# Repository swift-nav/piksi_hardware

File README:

Piksi Hardware
==============

Electronics design files for Swift Navigation projects - Eagle libraries,
schematics, and board files.

Copyright
=========

All files copyright (C) 2011-2013 Swift Navigation Inc.

License
=======

All files in this repository are licensed under the Creative Commons
Attribution Share-Alike 3.0 license - text available in LICENSE.

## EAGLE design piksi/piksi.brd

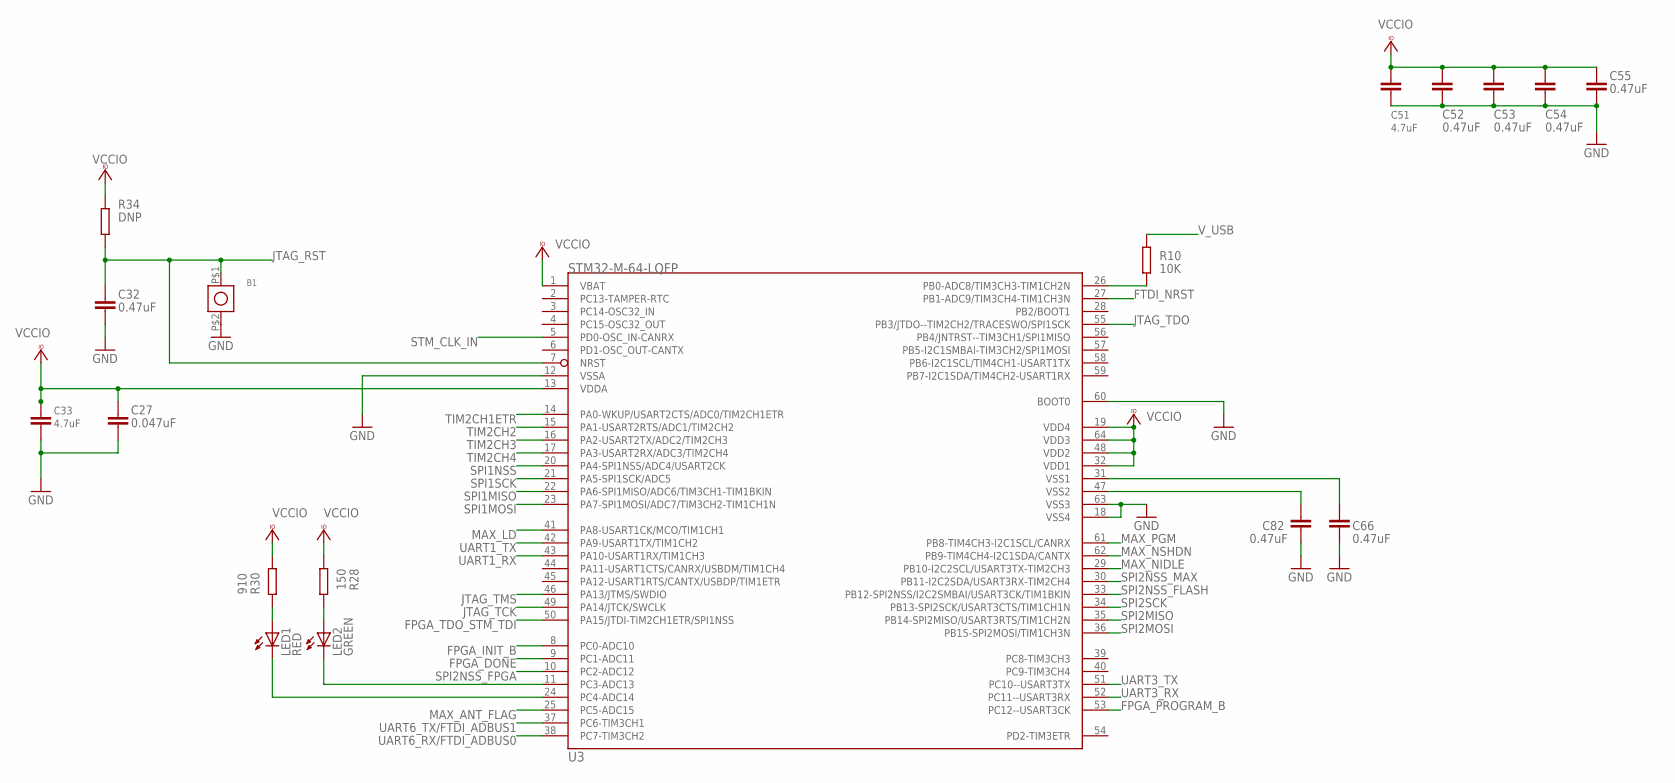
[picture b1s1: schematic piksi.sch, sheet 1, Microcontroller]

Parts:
B1: B3U-1000P
C27: 0.047uF; 0402-CAP
C32, C52, C53, C54, C55, C66, C82: 0.47uF; 0402-CAP
C33, C51: 4.7uF; 0603-CAP
LED1: RED; 0603-LED
LED2: GREEN; 0603-LED
R10: 10K; 0402-RES
R28: 150; 0402-RES
R30: 910; 0402-RES
R34: DNP; 0402-RES
U3: STM32-M-64-LQFP; LQFP64

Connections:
FPGA_DONE: U3.9 (PC1-ADC11); also elsewhere on the board
FPGA_INIT_B: U3.8 (PC0-ADC10); also elsewhere on the board
FPGA_PROGRAM_B: U3.53 (PC12--USART3CK); also elsewhere on the board
FPGA_TDO_STM_TDI: U3.50 (PA15/JTDI-TIM2CH1ETR/SPI1NSS); also elsewhere on the board
FTDI_NRST: U3.27 (PB1-ADC9/TIM3CH4-TIM1CH3N); also elsewhere on the board
GND: B1.P$2 (2), C27.P$2 (2), C32.P$2 (2), C33.P$1 (1), C51.P$1 (1), C52.P$2 (2), C53.P$2 (2), C54.P$2 (2), C55.P$2 (2), C66.P$2 (2), C82.P$1 (1), U3.12 (VSSA), U3.18 (VSS4), U3.60 (BOOT0), U3.63 (VSS3); also elsewhere on the board
JTAG_RST: B1.P$1 (1), C32.P$1 (1), R34.P$1 (1), U3.7 (NRST); also elsewhere on the board
JTAG_TCK: U3.49 (PA14/JTCK/SWCLK); also elsewhere on the board
JTAG_TDO: U3.55 (PB3/JTDO--TIM2CH2/TRACESWO/SPI1SCK); also elsewhere on the board
JTAG_TMS: U3.46 (PA13/JTMS/SWDIO); also elsewhere on the board
MAX_ANT_FLAG: U3.25 (PC5-ADC15); also elsewhere on the board
MAX_LD: U3.41 (PA8-USART1CK/MCO/TIM1CH1); also elsewhere on the board
MAX_NIDLE: U3.29 (PB10-I2C2SCL/USART3TX-TIM2CH3); also elsewhere on the board
MAX_NSHDN: U3.62 (PB9-TIM4CH4-I2C1SDA/CANTX); also elsewhere on the board
MAX_PGM: U3.61 (PB8-TIM4CH3-I2C1SCL/CANRX); also elsewhere on the board
unnamed: R10.P$1 (1), U3.26 (PB0-ADC8/TIM3CH3-TIM1CH2N)
unnamed: LED1.A, R30.P$1 (1)
unnamed: LED1.C, U3.24 (PC4-ADC14)
unnamed: LED2.A, R28.P$2 (2)
unnamed: LED2.C, U3.11 (PC3-ADC13)
SPI1MISO: U3.22 (PA6-SPI1MISO/ADC6/TIM3CH1-TIM1BKIN); also elsewhere on the board
SPI1MOSI: U3.23 (PA7-SPI1MOSI/ADC7/TIM3CH2-TIM1CH1N); also elsewhere on the board
SPI1NSS: U3.20 (PA4-SPI1NSS/ADC4/USART2CK); also elsewhere on the board
SPI1SCK: U3.21 (PA5-SPI1SCK/ADC5); also elsewhere on the board
SPI2MISO: U3.35 (PB14-SPI2MISO/USART3RTS/TIM1CH2N); also elsewhere on the board
SPI2MOSI: U3.36 (PB15-SPI2MOSI/TIM1CH3N); also elsewhere on the board
SPI2NSS_FLASH: U3.33 (PB12-SPI2NSS/I2C2SMBAI/USART3CK/TIM1BKIN); also elsewhere on the board
SPI2NSS_FPGA: U3.10 (PC2-ADC12)
SPI2NSS_MAX: U3.30 (PB11-I2C2SDA/USART3RX-TIM2CH4); also elsewhere on the board
SPI2SCK: U3.34 (PB13-SPI2SCK/USART3CTS/TIM1CH1N); also elsewhere on the board
STM_CLK_IN: U3.5 (PD0-OSC_IN-CANRX); also elsewhere on the board
TIM2CH1ETR: U3.14 (PA0-WKUP/USART2CTS/ADC0/TIM2CH1ETR); also elsewhere on the board
TIM2CH2: U3.15 (PA1-USART2RTS/ADC1/TIM2CH2); also elsewhere on the board
TIM2CH3: U3.16 (PA2-USART2TX/ADC2/TIM2CH3); also elsewhere on the board
TIM2CH4: U3.17 (PA3-USART2RX/ADC3/TIM2CH4); also elsewhere on the board
UART1_RX: U3.43 (PA10-USART1RX/TIM1CH3); also elsewhere on the board
UART1_TX: U3.42 (PA9-USART1TX/TIM1CH2); also elsewhere on the board
UART3_RX: U3.52 (PC11--USART3RX); also elsewhere on the board
UART3_TX: U3.51 (PC10--USART3TX); also elsewhere on the board
UART6_RX/FTDI_ADBUS0: U3.38 (PC7-TIM3CH2); also elsewhere on the board
UART6_TX/FTDI_ADBUS1: U3.37 (PC6-TIM3CH1); also elsewhere on the board
VCCIO: C27.P$1 (1), C33.P$2 (2), C51.P$2 (2), C52.P$1 (1), C53.P$1 (1), C54.P$1 (1), C55.P$1 (1), R28.P$1 (1), R30.P$2 (2), R34.P$2 (2), U3.1 (VBAT), U3.13 (VDDA), U3.19 (VDD4), U3.32 (VDD1), U3.48 (VDD2), U3.64 (VDD3); also elsewhere on the board
VSS1: C66.P$1 (1), U3.31 (VSS1)
VSS2: C82.P$2 (2), U3.47 (VSS2)
V_USB: R10.P$2 (2); also elsewhere on the board

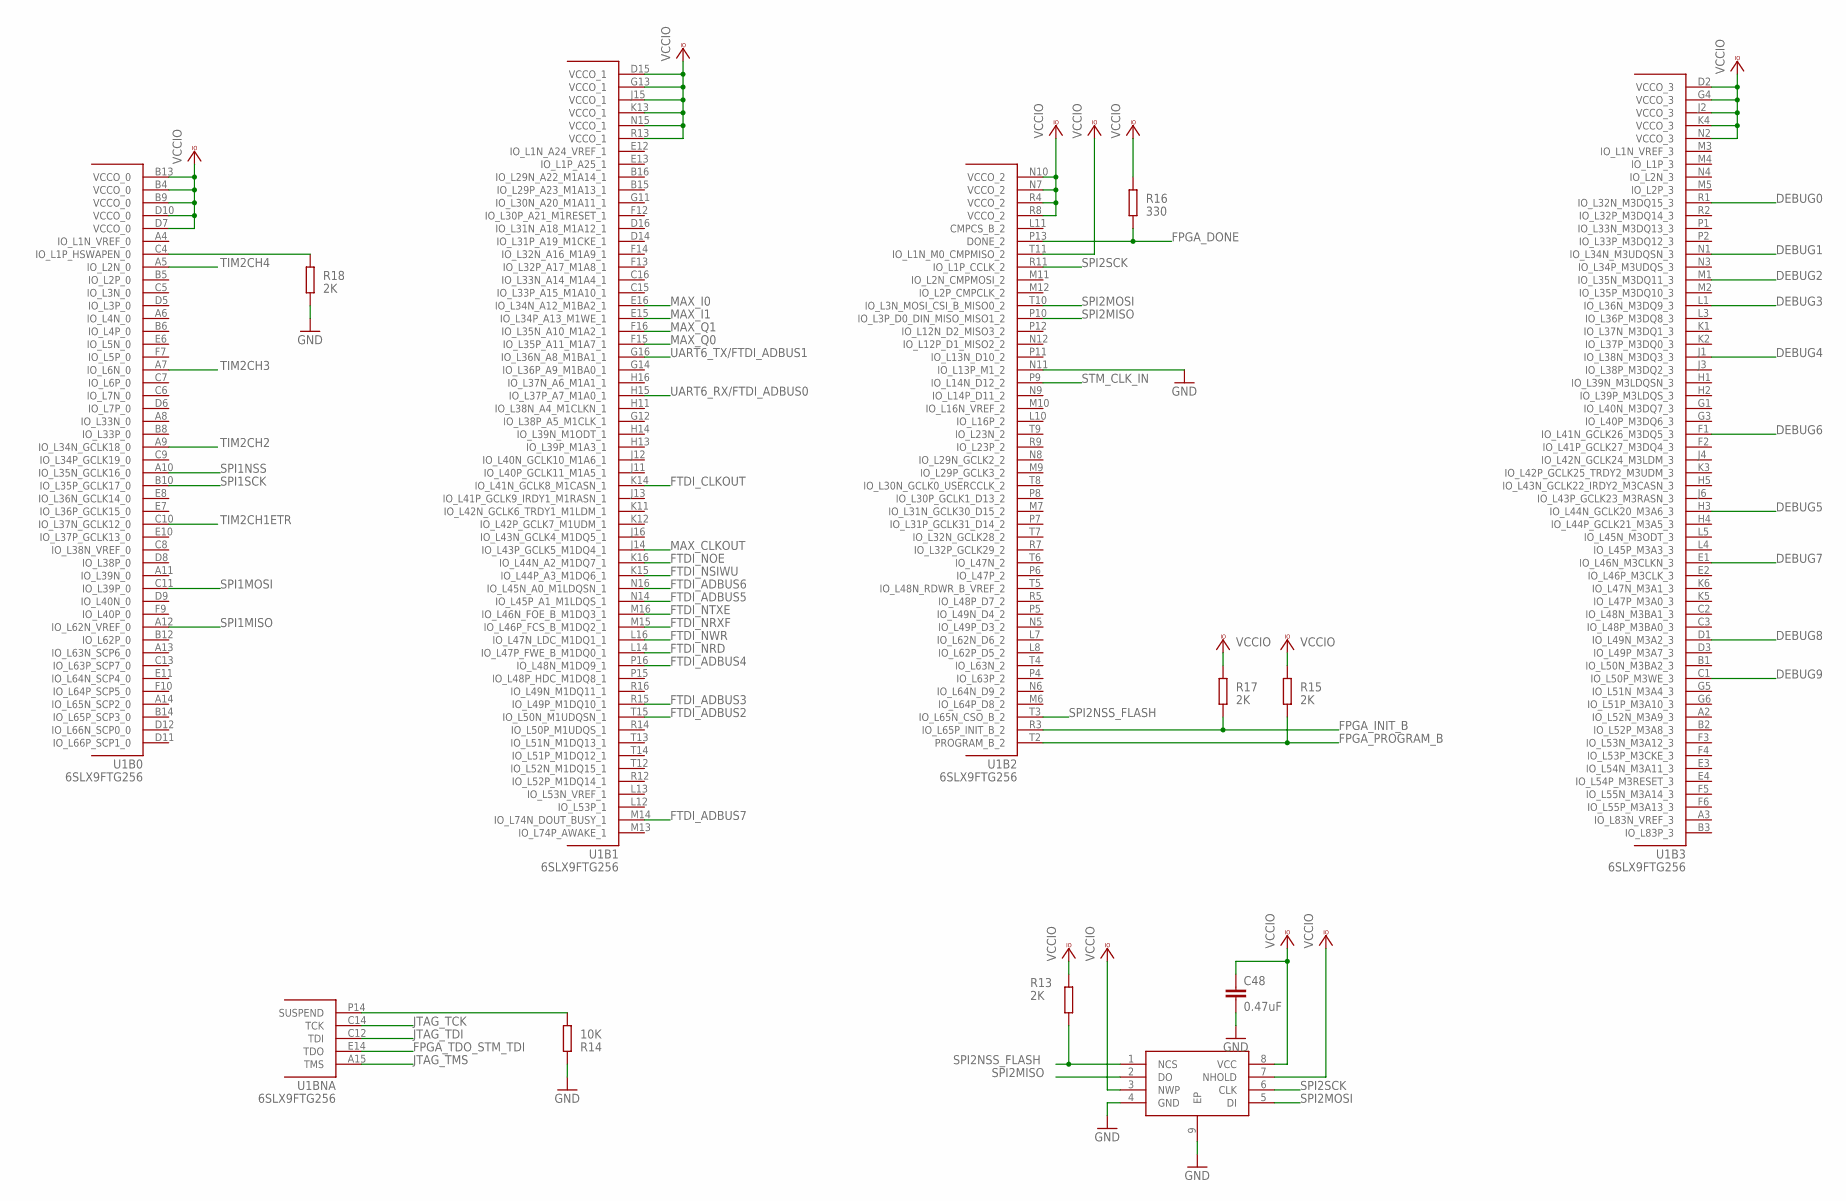
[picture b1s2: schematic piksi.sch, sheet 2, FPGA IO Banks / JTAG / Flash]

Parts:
C48: 0.47uF; 0402-CAP
R13, R15, R17, R18: 2K; 0402-RES
R14: 10K; 0402-RES
R16: 330; 0402-RES
U1: 6SLX9FTG256; FT256
U13: M25PX80; M25P80_MLP8

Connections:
DEBUG0: U1.R1 (IO_L32N_M3DQ15_3); also elsewhere on the board
DEBUG1: U1.N1 (IO_L34N_M3UDQSN_3); also elsewhere on the board
DEBUG2: U1.M1 (IO_L35N_M3DQ11_3); also elsewhere on the board
DEBUG3: U1.L1 (IO_L36N_M3DQ9_3); also elsewhere on the board
DEBUG4: U1.J1 (IO_L38N_M3DQ3_3); also elsewhere on the board
DEBUG5: U1.H3 (IO_L44N_GCLK20_M3A6_3); also elsewhere on the board
DEBUG6: U1.F1 (IO_L41N_GCLK26_M3DQ5_3); also elsewhere on the board
DEBUG7: U1.E1 (IO_L46N_M3CLKN_3); also elsewhere on the board
DEBUG8: U1.D1 (IO_L49N_M3A2_3); also elsewhere on the board
DEBUG9: U1.C1 (IO_L50P_M3WE_3); also elsewhere on the board
FPGA_DONE: R16.P$1 (1), U1.P13 (DONE_2); also elsewhere on the board
FPGA_INIT_B: R17.P$2 (2), U1.R3 (IO_L65P_INIT_B_2); also elsewhere on the board
FPGA_PROGRAM_B: R15.P$2 (2), U1.T2 (PROGRAM_B_2); also elsewhere on the board
FPGA_TDO_STM_TDI: U1.E14 (TDO); also elsewhere on the board
FTDI_ADBUS2: U1.T15 (IO_L50N_M1UDQSN_1); also elsewhere on the board
FTDI_ADBUS3: U1.R15 (IO_L49P_M1DQ10_1); also elsewhere on the board
FTDI_ADBUS4: U1.P16 (IO_L48N_M1DQ9_1); also elsewhere on the board
FTDI_ADBUS5: U1.N14 (IO_L45P_A1_M1LDQS_1); also elsewhere on the board
FTDI_ADBUS6: U1.N16 (IO_L45N_A0_M1LDQSN_1); also elsewhere on the board
FTDI_ADBUS7: U1.M14 (IO_L74N_DOUT_BUSY_1); also elsewhere on the board
FTDI_CLKOUT: U1.K14 (IO_L41N_GCLK8_M1CASN_1); also elsewhere on the board
FTDI_NOE: U1.K16 (IO_L44N_A2_M1DQ7_1); also elsewhere on the board
FTDI_NRD: U1.L14 (IO_L47P_FWE_B_M1DQ0_1); also elsewhere on the board
FTDI_NRXF: U1.M15 (IO_L46P_FCS_B_M1DQ2_1); also elsewhere on the board
FTDI_NSIWU: U1.K15 (IO_L44P_A3_M1DQ6_1); also elsewhere on the board
FTDI_NTXE: U1.M16 (IO_L46N_FOE_B_M1DQ3_1); also elsewhere on the board
FTDI_NWR: U1.L16 (IO_L47N_LDC_M1DQ1_1); also elsewhere on the board
GND: C48.P$2 (2), R14.P$2 (2), R18.P$1 (1), U1.N11 (IO_L13P_M1_2), U13.4 (GND), U13.9 (EP); also elsewhere on the board
JTAG_TCK: U1.C14 (TCK); also elsewhere on the board
JTAG_TDI: U1.C12 (TDI); also elsewhere on the board
JTAG_TMS: U1.A15 (TMS); also elsewhere on the board
MAX_CLKOUT: U1.J14 (IO_L43P_GCLK5_M1DQ4_1); also elsewhere on the board
MAX_I0: U1.E16 (IO_L34N_A12_M1BA2_1); also elsewhere on the board
MAX_I1: U1.E15 (IO_L34P_A13_M1WE_1); also elsewhere on the board
MAX_Q0: U1.F15 (IO_L35P_A11_M1A7_1); also elsewhere on the board
MAX_Q1: U1.F16 (IO_L35N_A10_M1A2_1); also elsewhere on the board
unnamed: R18.P$2 (2), U1.C4 (IO_L1P_HSWAPEN_0)
unnamed: R14.P$1 (1), U1.P14 (SUSPEND)
SPI1MISO: U1.A12 (IO_L62N_VREF_0); also elsewhere on the board
SPI1MOSI: U1.C11 (IO_L39P_0); also elsewhere on the board
SPI1NSS: U1.A10 (IO_L35N_GCLK16_0); also elsewhere on the board
SPI1SCK: U1.B10 (IO_L35P_GCLK17_0); also elsewhere on the board
SPI2MISO: U1.P10 (IO_L3P_D0_DIN_MISO_MISO1_2), U13.2 (DO); also elsewhere on the board
SPI2MOSI: U1.T10 (IO_L3N_MOSI_CSI_B_MISO0_2), U13.5 (DI); also elsewhere on the board
SPI2NSS_FLASH: R13.P$1 (1), U1.T3 (IO_L65N_CSO_B_2), U13.1 (NCS); also elsewhere on the board
SPI2SCK: U1.R11 (IO_L1P_CCLK_2), U13.6 (CLK); also elsewhere on the board
STM_CLK_IN: U1.P9 (IO_L14N_D12_2); also elsewhere on the board
TIM2CH1ETR: U1.C10 (IO_L37N_GCLK12_0); also elsewhere on the board
TIM2CH2: U1.A9 (IO_L34N_GCLK18_0); also elsewhere on the board
TIM2CH3: U1.A7 (IO_L6N_0); also elsewhere on the board
TIM2CH4: U1.A5 (IO_L2N_0); also elsewhere on the board
UART6_RX/FTDI_ADBUS0: U1.H15 (IO_L37P_A7_M1A0_1); also elsewhere on the board
UART6_TX/FTDI_ADBUS1: U1.G16 (IO_L36N_A8_M1BA1_1); also elsewhere on the board
VCCIO: C48.P$1 (1), R13.P$2 (2), R15.P$1 (1), R16.P$2 (2), R17.P$1 (1), U1.B4 (VCCO_0), U1.B9 (VCCO_0), U1.B13 (VCCO_0), U1.D2 (VCCO_3), U1.D7 (VCCO_0), U1.D10 (VCCO_0), U1.D15 (VCCO_1), U1.G4 (VCCO_3), U1.G13 (VCCO_1), U1.J2 (VCCO_3), U1.J15 (VCCO_1), U1.K4 (VCCO_3), U1.K13 (VCCO_1), U1.N2 (VCCO_3), U1.N7 (VCCO_2), U1.N10 (VCCO_2), U1.N15 (VCCO_1), U1.R4 (VCCO_2), U1.R8 (VCCO_2), U1.R13 (VCCO_1), U1.T11 (IO_L1N_M0_CMPMISO_2), U13.3 (NWP), U13.7 (NHOLD), U13.8 (VCC); also elsewhere on the board

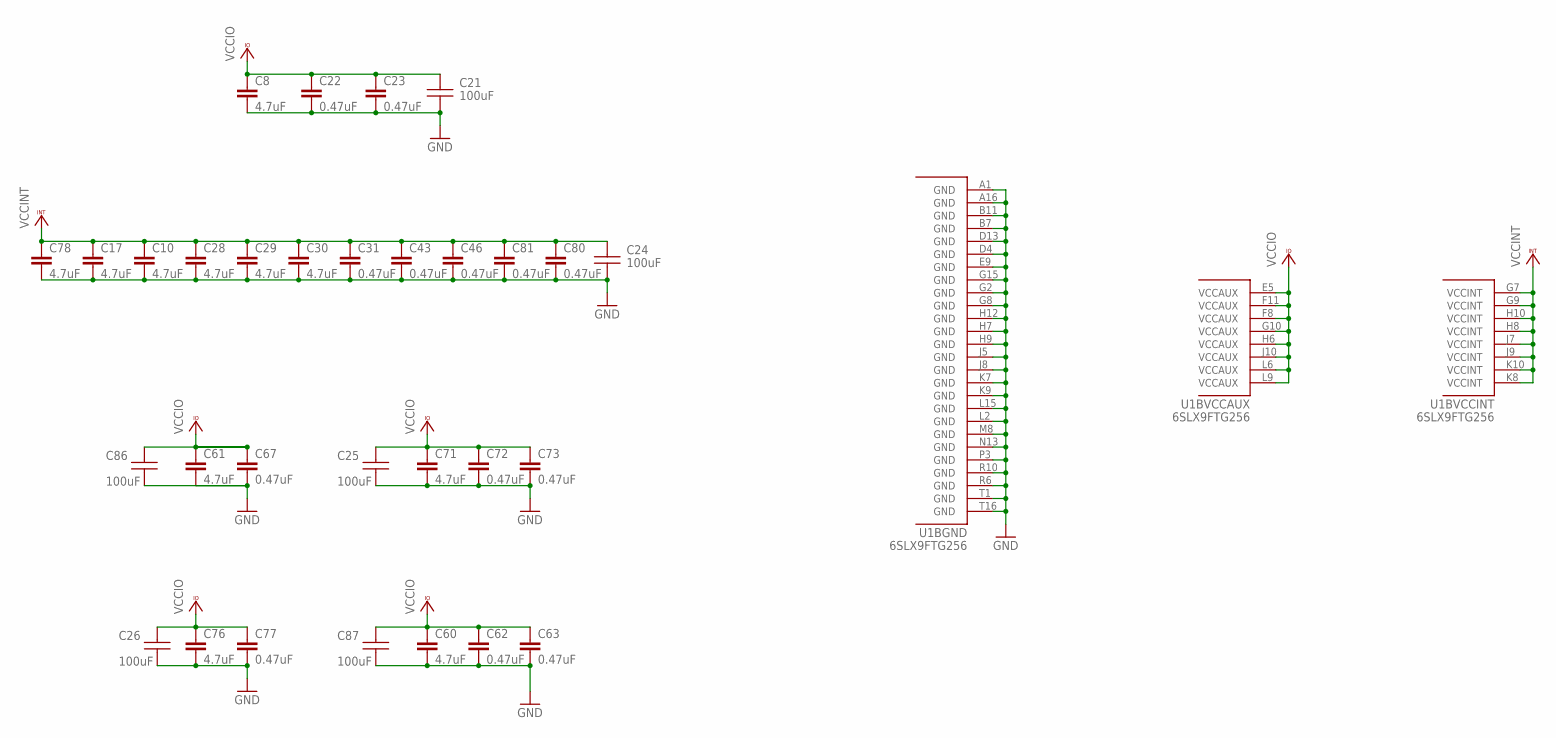
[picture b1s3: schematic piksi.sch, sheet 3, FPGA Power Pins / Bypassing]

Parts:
C8, C10, C17, C28, C29, C30, C60, C61, C71, C76, C78: 4.7uF; 0603-CAP
C21, C24, C25, C26, C86, C87: 100uF; C1210
C22, C23, C31, C43, C46, C62, C63, C67, C72, C73, C77, C80, C81: 0.47uF; 0402-CAP
U1: 6SLX9FTG256; FT256

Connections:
GND: C8.P$2 (2), C10.P$2 (2), C17.P$2 (2), C21.P$2 (2), C22.P$2 (2), C23.P$2 (2), C24.P$2 (2), C25.P$2 (2), C26.P$2 (2), C28.P$2 (2), C29.P$2 (2), C30.P$2 (2), C31.P$2 (2), C43.P$2 (2), C46.P$2 (2), C60.P$2 (2), C61.P$2 (2), C62.P$2 (2), C63.P$2 (2), C67.P$2 (2), C71.P$2 (2), C72.P$2 (2), C73.P$2 (2), C76.P$2 (2), C77.P$2 (2), C78.P$2 (2), C80.P$2 (2), C81.P$2 (2), C86.P$2 (2), C87.P$2 (2), U1.A1 (GND), U1.A16 (GND), U1.B7 (GND), U1.B11 (GND), U1.D4 (GND), U1.D13 (GND), U1.E9 (GND), U1.G2 (GND), U1.G8 (GND), U1.G15 (GND), U1.H7 (GND), U1.H9 (GND), U1.H12 (GND), U1.J5 (GND), U1.J8 (GND), U1.K7 (GND), U1.K9 (GND), U1.L2 (GND), U1.L15 (GND), U1.M8 (GND), U1.N13 (GND), U1.P3 (GND), U1.R6 (GND), U1.R10 (GND), U1.T1 (GND), U1.T16 (GND); also elsewhere on the board
VCCINT: C10.P$1 (1), C17.P$1 (1), C24.P$1 (1), C28.P$1 (1), C29.P$1 (1), C30.P$1 (1), C31.P$1 (1), C43.P$1 (1), C46.P$1 (1), C78.P$1 (1), C80.P$1 (1), C81.P$1 (1), U1.G7 (VCCINT), U1.G9 (VCCINT), U1.H8 (VCCINT), U1.H10 (VCCINT), U1.J7 (VCCINT), U1.J9 (VCCINT), U1.K8 (VCCINT), U1.K10 (VCCINT); also elsewhere on the board
VCCIO: C8.P$1 (1), C21.P$1 (1), C22.P$1 (1), C23.P$1 (1), C25.P$1 (1), C26.P$1 (1), C60.P$1 (1), C61.P$1 (1), C62.P$1 (1), C63.P$1 (1), C67.P$1 (1), C71.P$1 (1), C72.P$1 (1), C73.P$1 (1), C76.P$1 (1), C77.P$1 (1), C86.P$1 (1), C87.P$1 (1), U1.E5 (VCCAUX), U1.F8 (VCCAUX), U1.F11 (VCCAUX), U1.G10 (VCCAUX), U1.H6 (VCCAUX), U1.J10 (VCCAUX), U1.L6 (VCCAUX), U1.L9 (VCCAUX); also elsewhere on the board

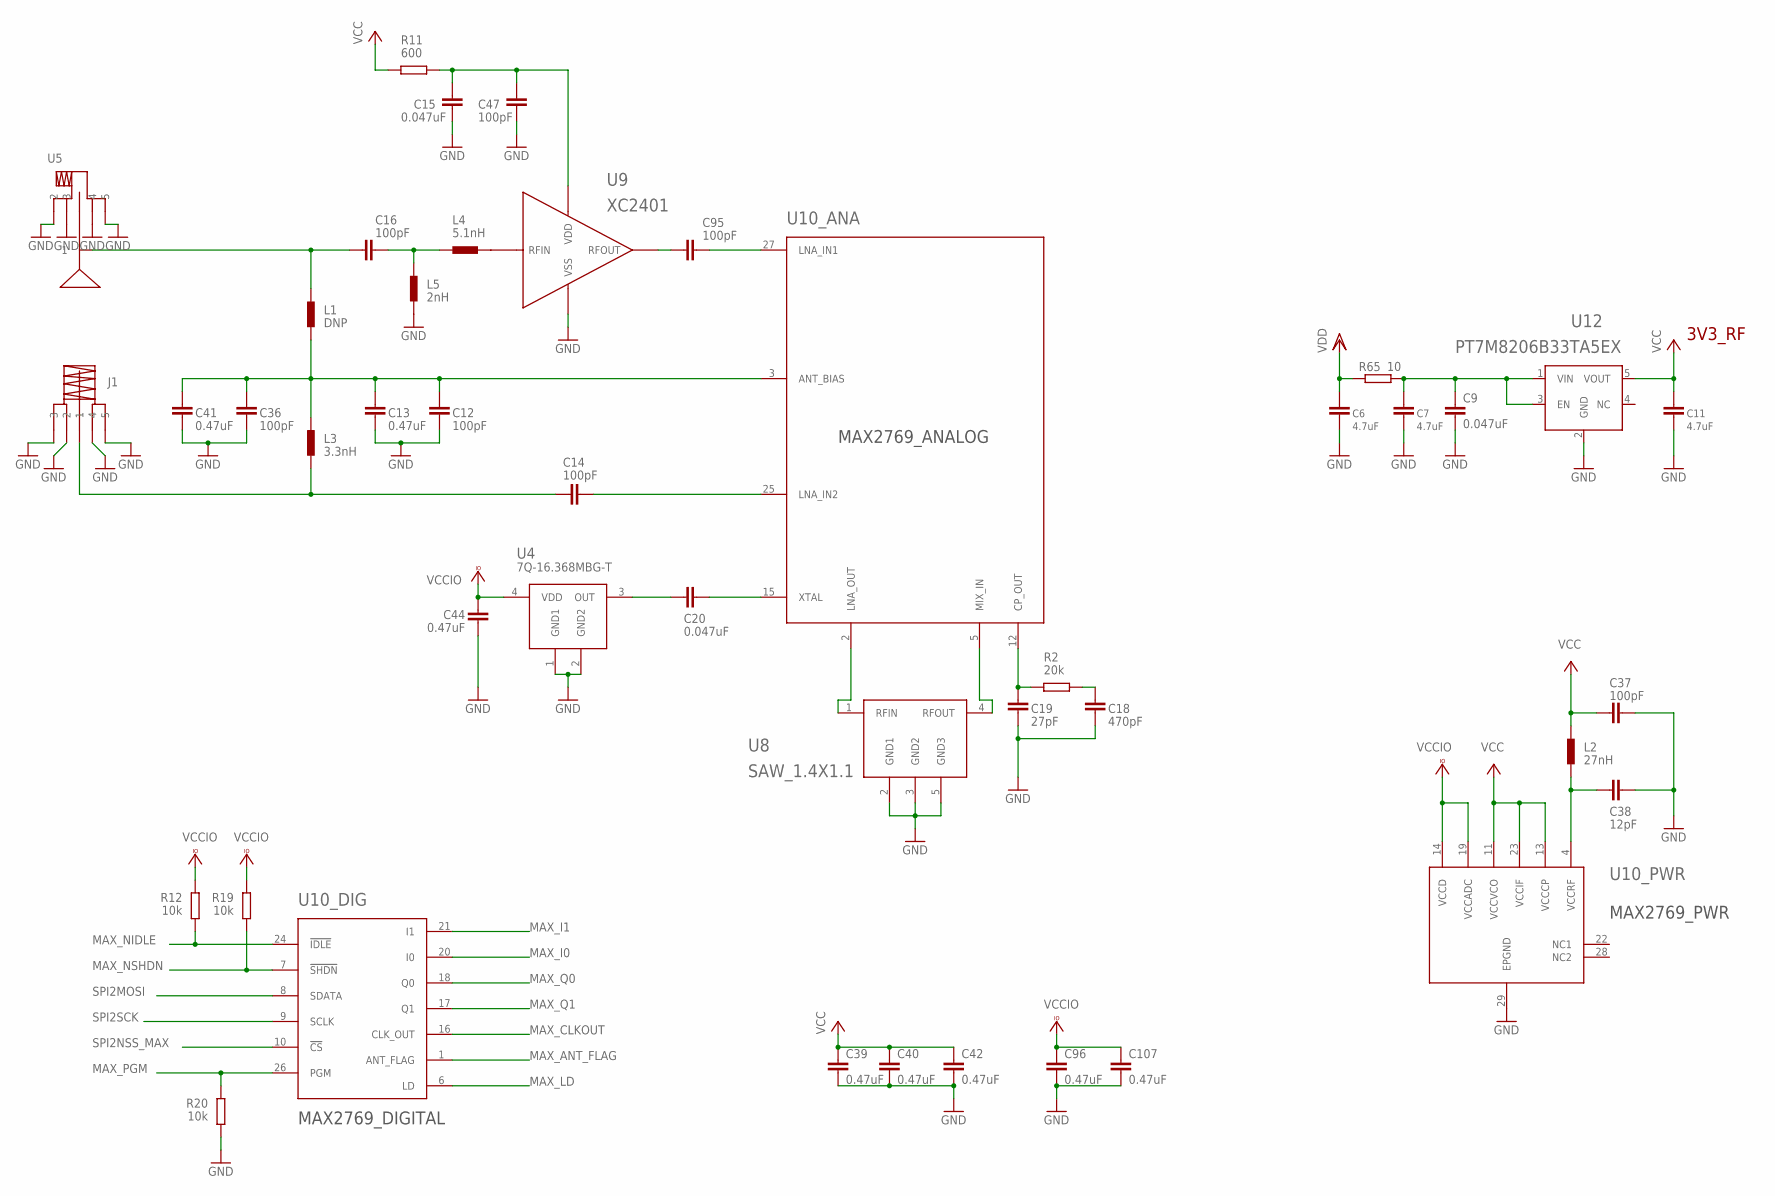
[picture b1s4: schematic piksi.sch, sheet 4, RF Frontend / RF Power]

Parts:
C6, C7, C11: 4.7uF; 0603-CAP
C9, C15, C20: 0.047uF; 0402-CAP
C12, C14, C16, C36, C37, C47, C95: 100pF; 0402-CAP
C13, C39, C40, C41, C42, C44, C96, C107: 0.47uF; 0402-CAP
C18: 470pF; 0402-CAP
C19: 27pF; 0402-CAP
C38: 12pF; 0402-CAP
J1: SMA_EDGE
L1: DNP; 0402-IND
L2: 27nH; 0402-IND
L3: 3.3nH; 0402-IND
L4: 5.1nH; 0402-IND
L5: 2nH; 0402-IND
R2: 20k; 0402-RES
R11: 600; 0402-RES
R12, R19, R20: 10k; 0402-RES
R65: 10; 0402-RES
U4: 7Q-16.368MBG-T; TCX_7Q
U5: SMA_PATCH_SMDGND
U8: SAW_1.4X1.1
U9: XC2401
U10: MAX2769
U12: PT7M8206B33TA5EX

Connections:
FE_CLK: C20.P$2 (2), U4.3 (OUT)
GND: C6.P$1 (1), C7.P$1 (1), C9.P$2 (2), C11.P$1 (1), C12.P$1 (1), C13.P$1 (1), C15.P$1 (1), C18.P$2 (2), C19.P$2 (2), C36.P$1 (1), C37.P$2 (2), C38.P$2 (2), C39.P$2 (2), C40.P$2 (2), C41.P$1 (1), C42.P$2 (2), C44.P$2 (2), C47.P$1 (1), C96.P$2 (2), C107.P$2 (2), J1.P2 (2), J1.P3 (3), J1.P4 (4), J1.P5 (5), L5.P$1 (1), R20.P$1 (1), U4.1 (GND1), U4.2 (GND2), U5.2, U5.3, U5.4, U5.5, U8.2 (GND1), U8.3 (GND2), U8.5 (GND3), U9.3 (VSS), U10.29 (EPGND), U12.2 (GND); also elsewhere on the board
MAX_ANT_FLAG: U10.1 (ANT_FLAG); also elsewhere on the board
MAX_CLKOUT: U10.16 (CLK_OUT); also elsewhere on the board
MAX_I0: U10.20 (I0); also elsewhere on the board
MAX_I1: U10.21 (I1); also elsewhere on the board
MAX_LD: U10.6 (LD); also elsewhere on the board
MAX_NIDLE: R12.P$1 (1), U10.24 (!IDLE); also elsewhere on the board
MAX_NSHDN: R19.P$1 (1), U10.7 (!SHDN); also elsewhere on the board
MAX_PGM: R20.P$2 (2), U10.26 (PGM); also elsewhere on the board
MAX_Q0: U10.18 (Q0); also elsewhere on the board
MAX_Q1: U10.17 (Q1); also elsewhere on the board
unnamed: L4.P$2 (2), U9.4 (RFIN)
unnamed: C18.P$1 (1), R2.P$1 (1)
unnamed: C19.P$1 (1), R2.P$2 (2), U10.12 (CP_OUT)
unnamed: U8.1 (RFIN), U10.2 (LNA_OUT)
unnamed: C20.P$1 (1), U10.15 (XTAL)
unnamed: U8.4 (RFOUT), U10.5 (MIX_IN)
unnamed: C14.P$1 (1), J1.P1 (1), L3.P$1 (1)
unnamed: C12.P$2 (2), C13.P$2 (2), C36.P$2 (2), C41.P$2 (2), L1.P$1 (1), L3.P$2 (2), U10.3 (ANT_BIAS)
unnamed: C95.P$2 (2), U10.27 (LNA_IN1)
unnamed: C16.P$1 (1), L1.P$2 (2), U5.1
unnamed: C38.P$1 (1), L2.P$1 (1), U10.4 (VCCRF)
unnamed: C14.P$2 (2), U10.25 (LNA_IN2)
unnamed: C16.P$2 (2), L4.P$1 (1), L5.P$2 (2)
unnamed: C95.P$1 (1), U9.2 (RFOUT)
unnamed: C15.P$2 (2), C47.P$2 (2), R11.P$1 (1), U9.1 (VDD)
unnamed: C7.P$2 (2), C9.P$1 (1), R65.P$2 (2), U12.1 (VIN), U12.3 (EN)
SPI2MOSI: U10.8 (SDATA); also elsewhere on the board
SPI2NSS_MAX: U10.10 (!CS); also elsewhere on the board
SPI2SCK: U10.9 (SCLK); also elsewhere on the board
VCC: C11.P$2 (2), C37.P$1 (1), C39.P$1 (1), C40.P$1 (1), C42.P$1 (1), L2.P$2 (2), R11.P$2 (2), U10.11 (VCCVCO), U10.13 (VCCCP), U10.23 (VCCIF), U12.5 (VOUT)
VCCIO: C44.P$1 (1), C96.P$1 (1), C107.P$1 (1), R12.P$2 (2), R19.P$2 (2), U4.4 (VDD), U10.14 (VCCD), U10.19 (VCCADC); also elsewhere on the board
VDD: C6.P$2 (2), R65.P$1 (1); also elsewhere on the board

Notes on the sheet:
3V3_RF

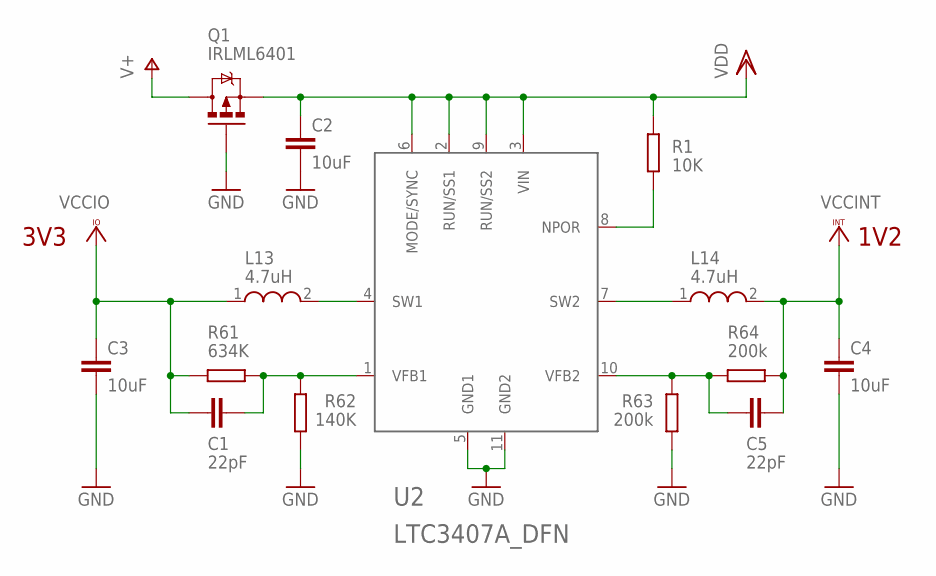
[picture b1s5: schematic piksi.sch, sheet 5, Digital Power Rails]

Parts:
C1, C5: 22pF; 0402-CAP
C2, C3, C4: 10uF; 1206-CAP
L13, L14: 4.7uH; LQM2HPN4R7MG0L
Q1: IRLML6401; SOT23-3
R1: 10K; 0402-RES
R61: 634K; 0402-RES
R62: 140K; 0402-RES
R63, R64: 200k; 0402-RES
U2: LTC3407A_DFN; DFN10

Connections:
GND: C2.P$2 (2), C3.P$2 (2), C4.P$2 (2), Q1.1 (G), R62.P$2 (2), R63.P$2 (2), U2.5 (GND1), U2.11 (GND2); also elsewhere on the board
unnamed: R1.P$1 (1), U2.8 (NPOR)
unnamed: L13.2, U2.4 (SW1)
unnamed: L14.1, U2.7 (SW2)
unnamed: C1.P$1 (1), R61.P$1 (1), R62.P$1 (1), U2.1 (VFB1)
unnamed: C5.P$2 (2), R63.P$1 (1), R64.P$1 (1), U2.10 (VFB2)
V+: Q1.3 (D); also elsewhere on the board
VCCINT: C4.P$1 (1), C5.P$1 (1), L14.2, R64.P$2 (2); also elsewhere on the board
VCCIO: C1.P$2 (2), C3.P$1 (1), L13.1, R61.P$2 (2); also elsewhere on the board
VDD: C2.P$1 (1), Q1.2 (S), R1.P$2 (2), U2.2 (RUN/SS1), U2.3 (VIN), U2.6 (MODE/SYNC), U2.9 (RUN/SS2); also elsewhere on the board

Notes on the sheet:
1V2
3V3

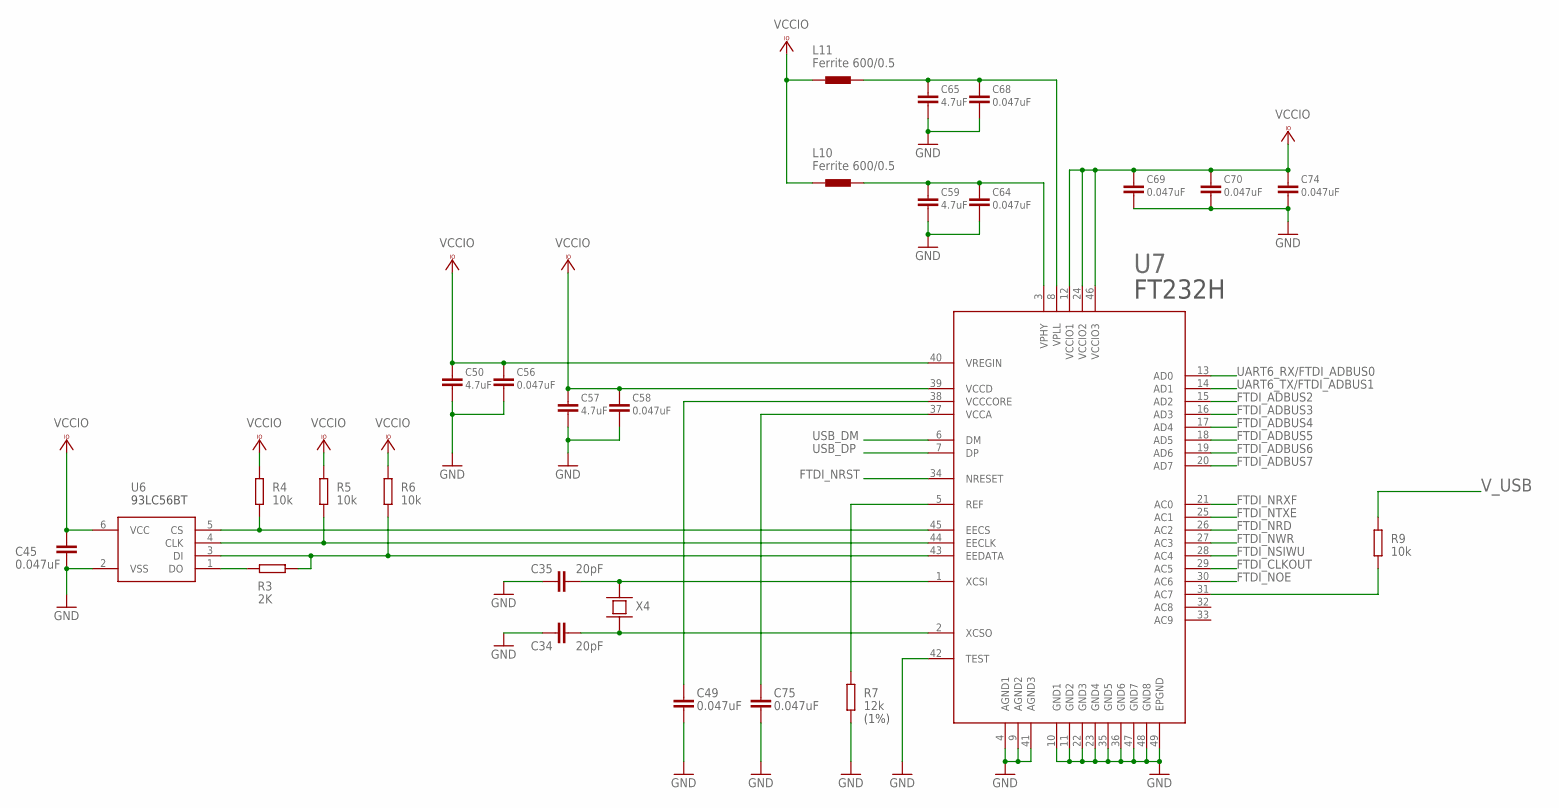
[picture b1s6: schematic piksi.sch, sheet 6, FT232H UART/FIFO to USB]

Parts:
C34, C35: 20pF; 0402-CAP
C45: 0.047uF; C0402
C49, C56, C58, C64, C68, C70, C74, C75: 0.047uF; 0402-CAP
C50, C57, C59, C65: 4.7uF; 0603-CAP
C69: 0.047uF; C0603K
L10, L11: Ferrite 600/0.5; 0805-IND
R3: 2K; 0402-RES
R4, R5, R6, R9: 10k; 0402-RES
R7: 12k; 0402-RES
U6: 93LC56BT-I/OT; 93AA56BT-I/OT
U7: FT232HQ
X4: NX5032GA-12M; NX5032GA

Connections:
FTDI_ADBUS2: U7.15 (AD2); also elsewhere on the board
FTDI_ADBUS3: U7.16 (AD3); also elsewhere on the board
FTDI_ADBUS4: U7.17 (AD4); also elsewhere on the board
FTDI_ADBUS5: U7.18 (AD5); also elsewhere on the board
FTDI_ADBUS6: U7.19 (AD6); also elsewhere on the board
FTDI_ADBUS7: U7.20 (AD7); also elsewhere on the board
FTDI_CLKOUT: U7.29 (AC5); also elsewhere on the board
FTDI_NOE: U7.30 (AC6); also elsewhere on the board
FTDI_NRD: U7.26 (AC2); also elsewhere on the board
FTDI_NRST: U7.34 (NRESET); also elsewhere on the board
FTDI_NRXF: U7.21 (AC0); also elsewhere on the board
FTDI_NSIWU: U7.28 (AC4); also elsewhere on the board
FTDI_NTXE: U7.25 (AC1); also elsewhere on the board
FTDI_NWR: U7.27 (AC3); also elsewhere on the board
GND: C34.P$2 (2), C35.P$2 (2), C45.2, C49.P$2 (2), C50.P$1 (1), C56.P$2 (2), C57.P$1 (1), C58.P$2 (2), C59.P$1 (1), C64.P$2 (2), C65.P$1 (1), C68.P$2 (2), C69.2, C70.P$2 (2), C74.P$2 (2), C75.P$2 (2), R7.P$2 (2), U6.2 (VSS), U7.4 (AGND1), U7.9 (AGND2), U7.10 (GND1), U7.11 (GND2), U7.22 (GND3), U7.23 (GND4), U7.35 (GND5), U7.36 (GND6), U7.41 (AGND3), U7.42 (TEST), U7.47 (GND7), U7.48 (GND8), U7.49 (EPGND); also elsewhere on the board
unnamed: C34.P$1 (1), U7.2 (XCSO), X4.2
unnamed: C35.P$1 (1), U7.1 (XCSI), X4.1
unnamed: C49.P$1 (1), U7.38 (VCCCORE)
unnamed: R9.P$2 (2), U7.31 (AC7)
unnamed: C65.P$2 (2), C68.P$1 (1), L11.P$2 (2), U7.8 (VPLL)
unnamed: R4.P$2 (2), U6.5 (CS), U7.45 (EECS)
unnamed: R5.P$2 (2), U6.4 (CLK), U7.44 (EECLK)
unnamed: R3.P$1 (1), R6.P$2 (2), U6.3 (DI), U7.43 (EEDATA)
unnamed: R3.P$2 (2), U6.1 (DO)
unnamed: C59.P$2 (2), C64.P$1 (1), L10.P$2 (2), U7.3 (VPHY)
unnamed: C75.P$1 (1), U7.37 (VCCA)
unnamed: R7.P$1 (1), U7.5 (REF)
UART6_RX/FTDI_ADBUS0: U7.13 (AD0); also elsewhere on the board
UART6_TX/FTDI_ADBUS1: U7.14 (AD1); also elsewhere on the board
USB_DM: U7.6 (DM); also elsewhere on the board
USB_DP: U7.7 (DP); also elsewhere on the board
VCCIO: C45.1, C50.P$2 (2), C56.P$1 (1), C57.P$2 (2), C58.P$1 (1), C69.1, C70.P$1 (1), C74.P$1 (1), L10.P$1 (1), L11.P$1 (1), R4.P$1 (1), R5.P$1 (1), R6.P$1 (1), U6.6 (VCC), U7.12 (VCCIO1), U7.24 (VCCIO2), U7.39 (VCCD), U7.40 (VREGIN), U7.46 (VCCIO3); also elsewhere on the board
V_USB: R9.P$1 (1); also elsewhere on the board

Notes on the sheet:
(1%)

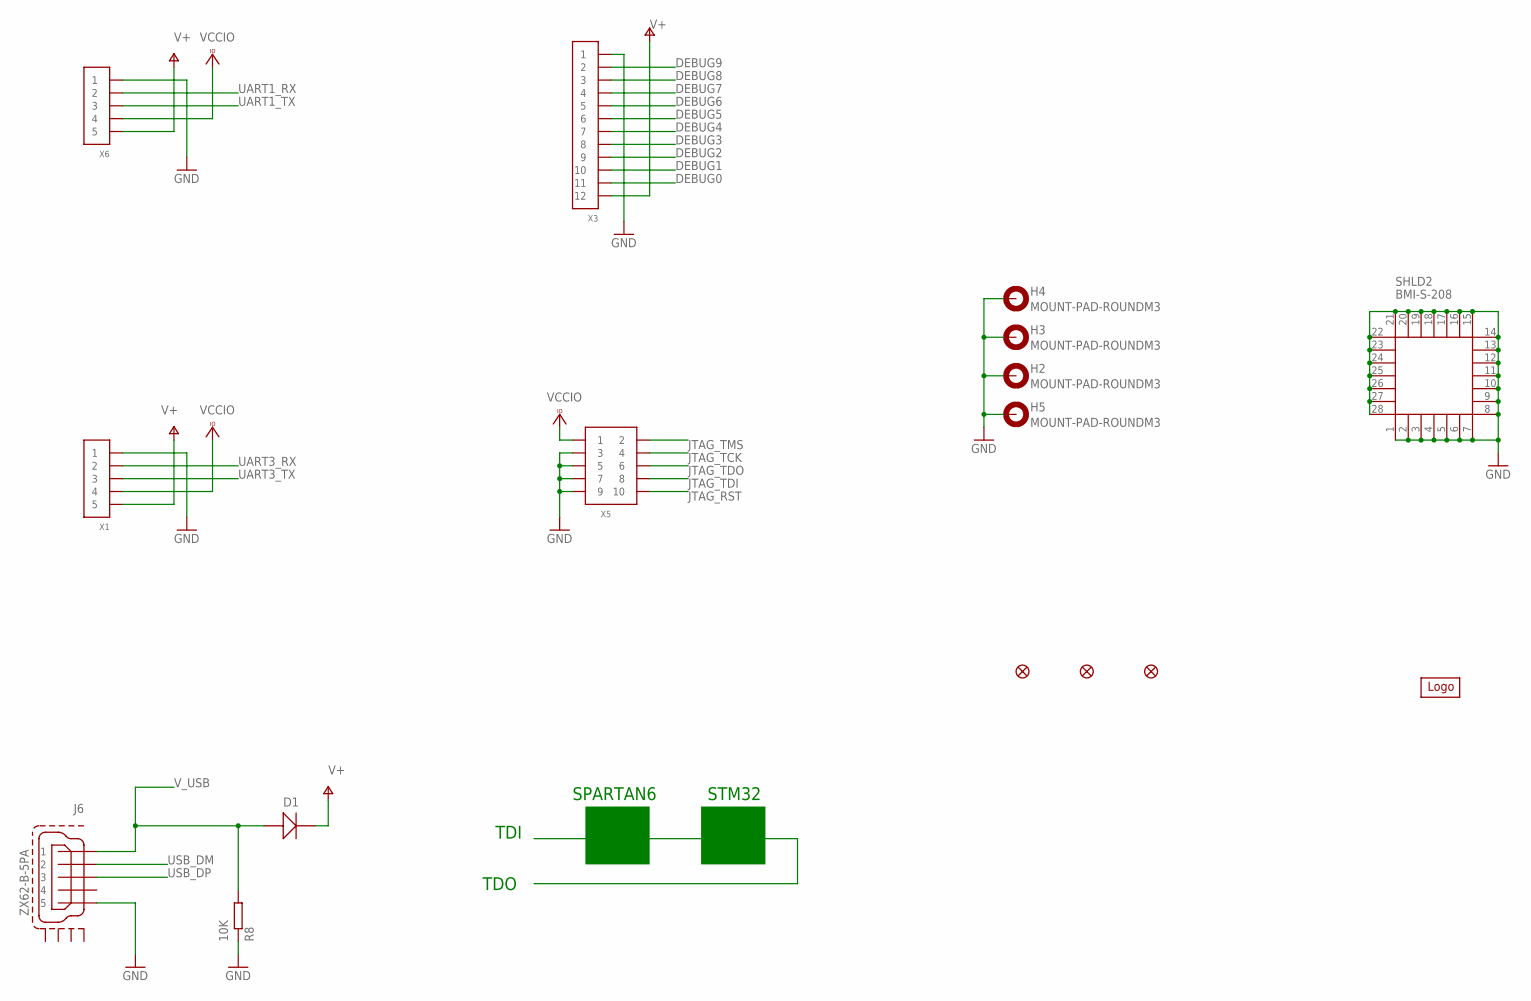
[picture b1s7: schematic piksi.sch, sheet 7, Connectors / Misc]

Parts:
D1: MBR0520; SOD-123
H2, H3, H4, H5: MOUNT-PAD-ROUNDM3; M3-PAD
J6: ZX62-B-5PA
JP8, JP9, JP10: FIDUCIAL1.5X3; FIDUCIAL-1.5X3
R8: 10K; 0402-RES
SHLD2: BMI-S-208
U$2: LOGOLOGO3_SMALL; LOGO3_SMALL
X1, X6: CONN_5-1-53261; PB-53261-05
X3: FPGA DEBUG; PB-53261-12
X5: CONN_5-2; FTSH-105-D

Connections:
DEBUG0: X3.11; also elsewhere on the board
DEBUG1: X3.10; also elsewhere on the board
DEBUG2: X3.9; also elsewhere on the board
DEBUG3: X3.8; also elsewhere on the board
DEBUG4: X3.7; also elsewhere on the board
DEBUG5: X3.6; also elsewhere on the board
DEBUG6: X3.5; also elsewhere on the board
DEBUG7: X3.4; also elsewhere on the board
DEBUG8: X3.3; also elsewhere on the board
DEBUG9: X3.2; also elsewhere on the board
GND: H2.B3,0, H3.B3,0, H4.B3,0, H5.B3,0, J6.PIN_5 (5), R8.P$1 (1), SHLD2.1, SHLD2.2, SHLD2.3, SHLD2.4, SHLD2.5, SHLD2.6, SHLD2.7, SHLD2.8, SHLD2.9, SHLD2.10, SHLD2.11, SHLD2.12, SHLD2.13, SHLD2.14, SHLD2.15, SHLD2.16, SHLD2.17, SHLD2.18, SHLD2.19, SHLD2.20, SHLD2.21, SHLD2.22, SHLD2.23, SHLD2.24, SHLD2.25, SHLD2.26, SHLD2.27, SHLD2.28, X1.1, X3.1, X5.3, X5.5, X5.7, X5.9, X6.1; also elsewhere on the board
JTAG_RST: X5.10; also elsewhere on the board
JTAG_TCK: X5.4; also elsewhere on the board
JTAG_TDI: X5.8; also elsewhere on the board
JTAG_TDO: X5.6; also elsewhere on the board
JTAG_TMS: X5.2; also elsewhere on the board
UART1_RX: X6.2; also elsewhere on the board
UART1_TX: X6.3; also elsewhere on the board
UART3_RX: X1.2; also elsewhere on the board
UART3_TX: X1.3; also elsewhere on the board
USB_DM: J6.PIN_2 (2); also elsewhere on the board
USB_DP: J6.PIN_3 (3); also elsewhere on the board
V+: D1.2, X1.5, X3.12, X6.5; also elsewhere on the board
VCCIO: X1.4, X5.1, X6.4; also elsewhere on the board
V_USB: D1.1, J6.PIN_1 (1), R8.P$2 (2); also elsewhere on the board

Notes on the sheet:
TDI
TDO
STM32
SPARTAN6

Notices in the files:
piksi/piksi.sch:
License : CC BY-SA 3.0
parts and their libraries:
SparkFun-DiscreteSemi: Licensing: CC v3.0 Share-Alike You are welcome to use this library for commercial purposes.
